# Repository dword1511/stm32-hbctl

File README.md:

# STM32-based half-bridge controller

This firmware code uses an `STM32F042` MCU to generate waveform for a STMicro `L6498` half-bridge driver,
which drives the MOSFETs in the inverter.

This particular inverter delivers 1 MHz AC current for our capacitive power transfer (CPT) project.
It has onboard buttons allowing us to cycle through 1 MHz +/- 100 kHz, with a few kHz of resolution.
It also has USB for ISP/DFU.

Unusual things this firmware does:

* Using HSI48 trimming in conjunction with timer prescaler to deliver a resolution of a few kHz across a large frequency range.
* Using a generic timer (rather than the advanced one) to generate complementary waveforms with dead time.

## General Build Instructions

You will need the following packages (Debian/Ubuntu):

* build-essential
* gcc-arm-none-eabi
* git
* dfu-util

The firmware can be loaded via USB DFU. However, you can also flash and debug via SWD. To do so, install the following package:

* stlink-tools
* gdb-multiarch

This project uses `libopencm3`. It will be automatically checked out during the building process.
To build the firmware, run `make`. To flash it, hold the `ISP/USR` button on the board, connect the board to USB, and then run `make flash-dfu`.

## Special Directions for CPT

Please be aware of the high voltage, especially at matching network's output.

Connect the inverter to the matching network first. Do not power on the inverter without any load.
Connect 12 V DC power to the 12 V port with a 4 mm banana test lead. Connect a variable DC power source to the HV port. Connect the ground together to GND.

Power the board on and observe the LEDs starting to flash. Use the `ISP/USR` button to enable the half-bridge. Then use the same button to cycle through frequencies.
The matching network reaches resonance when the output voltage peaks. Bridge current can be monitored by attaching an oscilloscope probe to the `CSP` pin.

## Publication

This project was part of the following work. Please kindly consider citing the paper as shown:

```
@inproceedings{Capttery,
 author = {Zhang, Chi and Kumar, Sidharth and Bharadia, Dinesh},
 title = {{Capttery: Scalable Battery-like Room-level Wireless Power}},
 booktitle = {Proc. of ACM MobiSys},
 year = {2019},
}
```

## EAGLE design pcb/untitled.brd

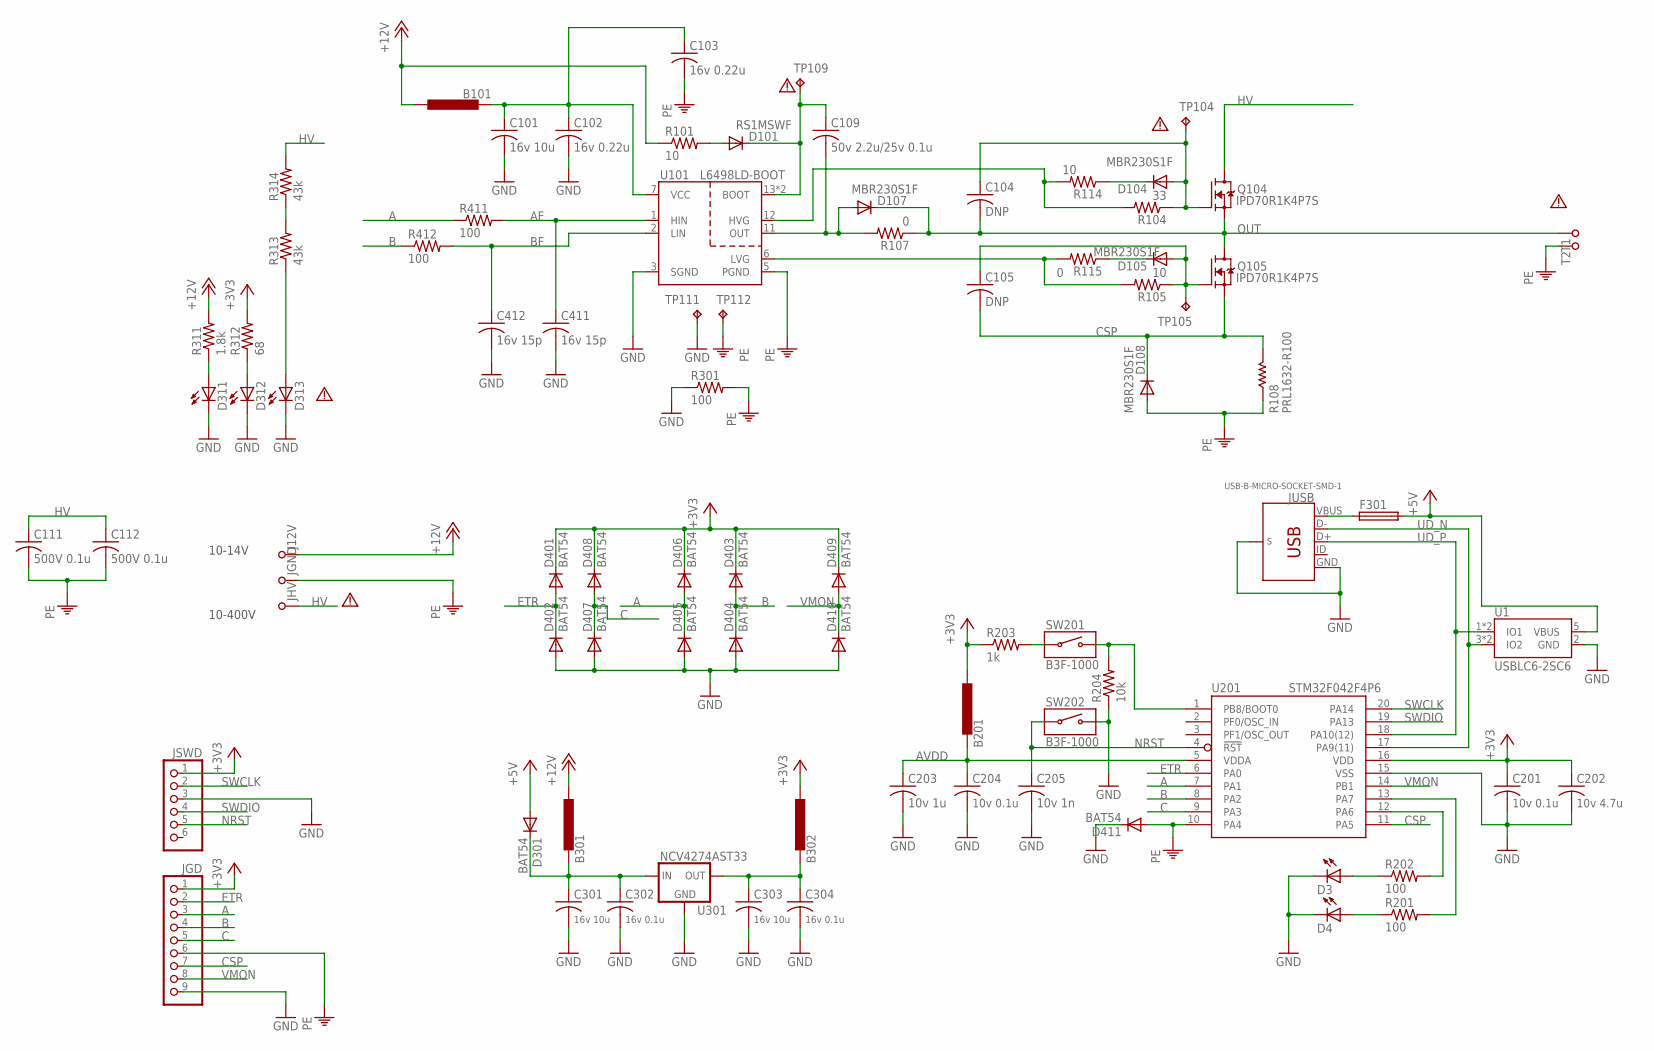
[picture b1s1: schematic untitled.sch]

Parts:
B101, B201, B301, B302: BEAD-0603; 0603
C101, C301, C303: 16v 10u; C0805
C102, C103: 16v 0.22u; C0603
C104, C105: DNP; C0603
C109: 50v 2.2u/25v 0.1u; C0805
C111, C112: 500V 0.1u; C1210
C201, C204: 10v 0.1u; C0603
C202: 10v 4.7u; C0603
C203: 10v 1u; C0603
C205: 10v 1n; C0603
C302, C304: 16v 0.1u; C0603
C411, C412: 16v 15p; C0603
D3, D4, D311, D312, D313: LEDSML0603; SML0603
D101: RS1MSWF; SOD123
D104, D105, D107, D108: MBR230S1F; SOD123
D301, D401, D402, D403, D404, D405, D406, D407, D408, D409, D410, D411: BAT54; SOD323-R
F301: FUSE-0603; 0603
J12V: BANANA_JACKKEYSTONE-575; KEYSTONE-575
JGD: PINHD-1X9/90; 1X09/90
JGND: BANANA_JACKKEYSTONE-575; KEYSTONE-575
JHV: BANANA_JACKKEYSTONE-575; KEYSTONE-575
JSWD: PINHD-1X6/90; 1X06/90
JUSB: USB-B-MICRO-SOCKET-SMD-1
Q104, Q105: IPD70R1K4P7S; TO-252AA
R101, R105, R114: 10; R0603
R104: 33; R0603
R107, R115: 0; R0603
R108: PRL1632-R100; 1206W
R201, R202, R301, R411, R412: 100; R0603
R203: 1k; R0603
R204: 10k; R0603
R311: 1.8k; R0603
R312: 68; R0603
R313, R314: 43k; R0603
SILK1, SILK2, SILK7, SILK11, SILK14: CAUTION-1.3MM
SW201, SW202: B3F-1000; B3F-10XX
T1, T2: TP; PAD-7.5X2.5
TP104, TP105, TP109, TP111, TP112: TPPAD1-13; P1-13
U1: USBLC6-2SC6; SOT-23-6
U101: L6498LD-BOOT; SOIC-14
U201: STM32F042F4P6; TSSOP-20
U301: NCV4274AST33; SOT-223

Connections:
+3V3: B201.2, B302.2, C201.1, C202.1, D401.C, D403.C, D406.C, D408.C, D409.C, JGD.1, JSWD.1, R203.1, R312.2, U201.16 (VDD)
+5V: D301.A, F301.2, U1.5 (VBUS)
+12V: B101.2, B301.2, J12V.P$1, R101.1, R311.2
A: D405.C, D406.A, JGD.3, R411.1, U201.7 (PA1)
AF: C411.1, R411.2, U101.1 (HIN)
AVDD: B201.1, C203.1, C204.1, U201.5 (VDDA)
B: D403.A, D404.C, JGD.4, R412.1, U201.8 (PA2)
BF: C412.1, R412.2, U101.2 (LIN)
C: D407.C, D408.A, JGD.5, U201.9 (PA3)
CSP: C105.2, D108.C, JGD.7, Q105.3 (S), R108.2, U201.11 (PA5)
ETR: D401.A, D402.C, JGD.2, U201.6 (PA0)
GND: C101.2, C102.2, C201.2, C202.2, C203.2, C204.2, C205.2, C301.2, C302.2, C303.2, C304.2, C411.2, C412.2, D3.C, D4.C, D311.C, D312.C, D313.C, D402.A, D404.A, D405.A, D407.A, D410.A, D411.C, JGD.9, JSWD.3, JUSB.GND, JUSB.MT1 (SHIELD), JUSB.MT2 (SHIELD), JUSB.P$1 (SHIELD), JUSB.P$2 (SHIELD), R204.1, R301.1, SW202.3 (B), SW202.4 (B), TP111.TP, U1.2 (GND), U101.3 (SGND), U201.15 (VSS), U301.2 (GND), U301.4 (GND)
HV: C111.1, C112.1, JHV.P$1, Q104.4 (D), R314.2
unnamed: D101.A, R101.2
unnamed: D105.C, R115.1
unnamed: R313.2, R314.1
unnamed: R105.2, R115.2, U101.6 (LVG)
unnamed: C105.1, D105.A, Q105.1 (G), R105.1, TP105.TP
unnamed: D104.C, R114.1
unnamed: R203.2, SW201.1 (COM), SW201.2 (COM)
unnamed: D3.A, R202.1
unnamed: C109.1, D101.C, TP109.TP, U101.13 (BOOT), U101.14 (BOOT)
unnamed: D4.A, R201.1
unnamed: R204.2, SW201.3 (B), SW201.4 (B), U201.1 (PB8/BOOT0)
unnamed: B301.1, C301.1, C302.1, D301.C, U301.1 (IN)
unnamed: F301.1, JUSB.VBUS
unnamed: R202.2, U201.12 (PA6)
unnamed: B302.1, C303.1, C304.1, U301.3 (OUT)
unnamed: B101.1, C101.1, C102.1, C103.1, U101.7 (VCC)
unnamed: R201.2, U201.13 (PA7)
unnamed: D313.A, R313.1
unnamed: C104.1, D104.A, Q104.1 (G), R104.1, TP104.TP
unnamed: R104.2, R114.2, U101.12 (HVG)
unnamed: C109.2, D107.A, R107.2, U101.11 (OUT)
unnamed: D312.A, R312.1
unnamed: D311.A, R311.1
NRST: C205.1, JSWD.5, SW202.1 (COM), SW202.2 (COM), U201.4 (!RST!)
OUT: C104.2, D107.C, Q104.3 (S), Q105.4 (D), R107.1, T1.1
PE: C103.2, C111.2, C112.2, D108.A, D411.A, JGD.6, JGND.P$1, R108.1, R301.2, T2.1, TP112.TP, U101.5 (PGND), U201.10 (PA4)
SWCLK: JSWD.2, U201.20 (PA14)
SWDIO: JSWD.4, U201.19 (PA13)
UD_N: JUSB.D-, U1.3 (IO2), U1.4 (IO2), U201.17 (PA9(11))
UD_P: JUSB.D+, U1.1 (IO1), U1.6 (IO1), U201.18 (PA10(12))
VMON: D409.A, D410.C, JGD.8, U201.14 (PB1)

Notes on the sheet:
10-14V
10-400V

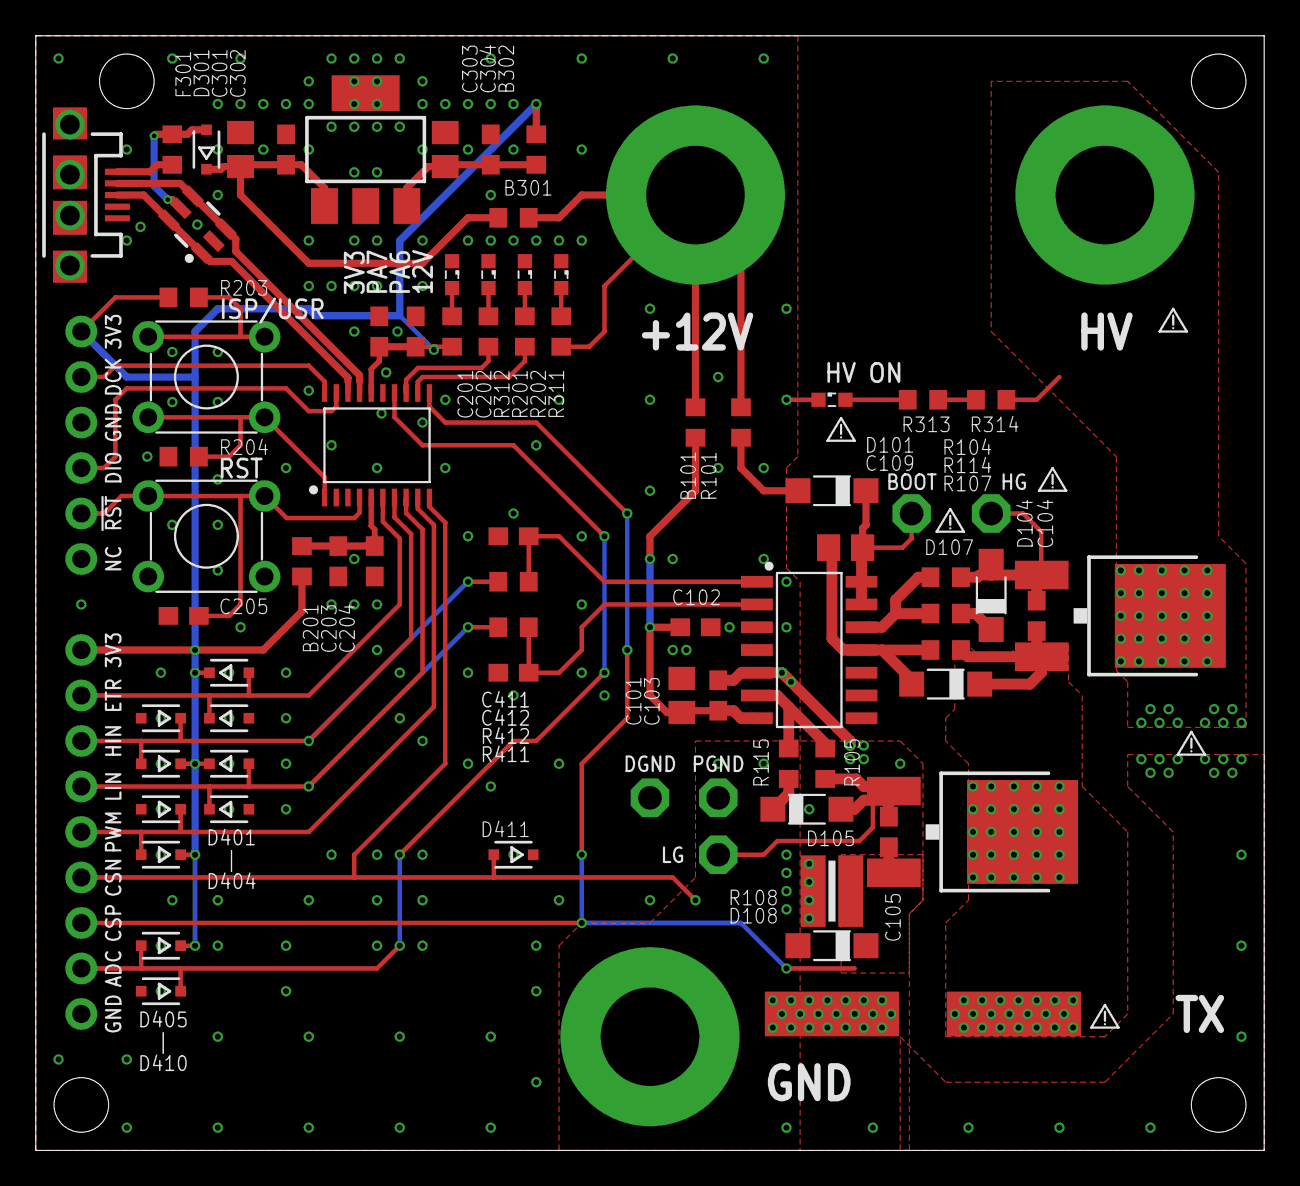
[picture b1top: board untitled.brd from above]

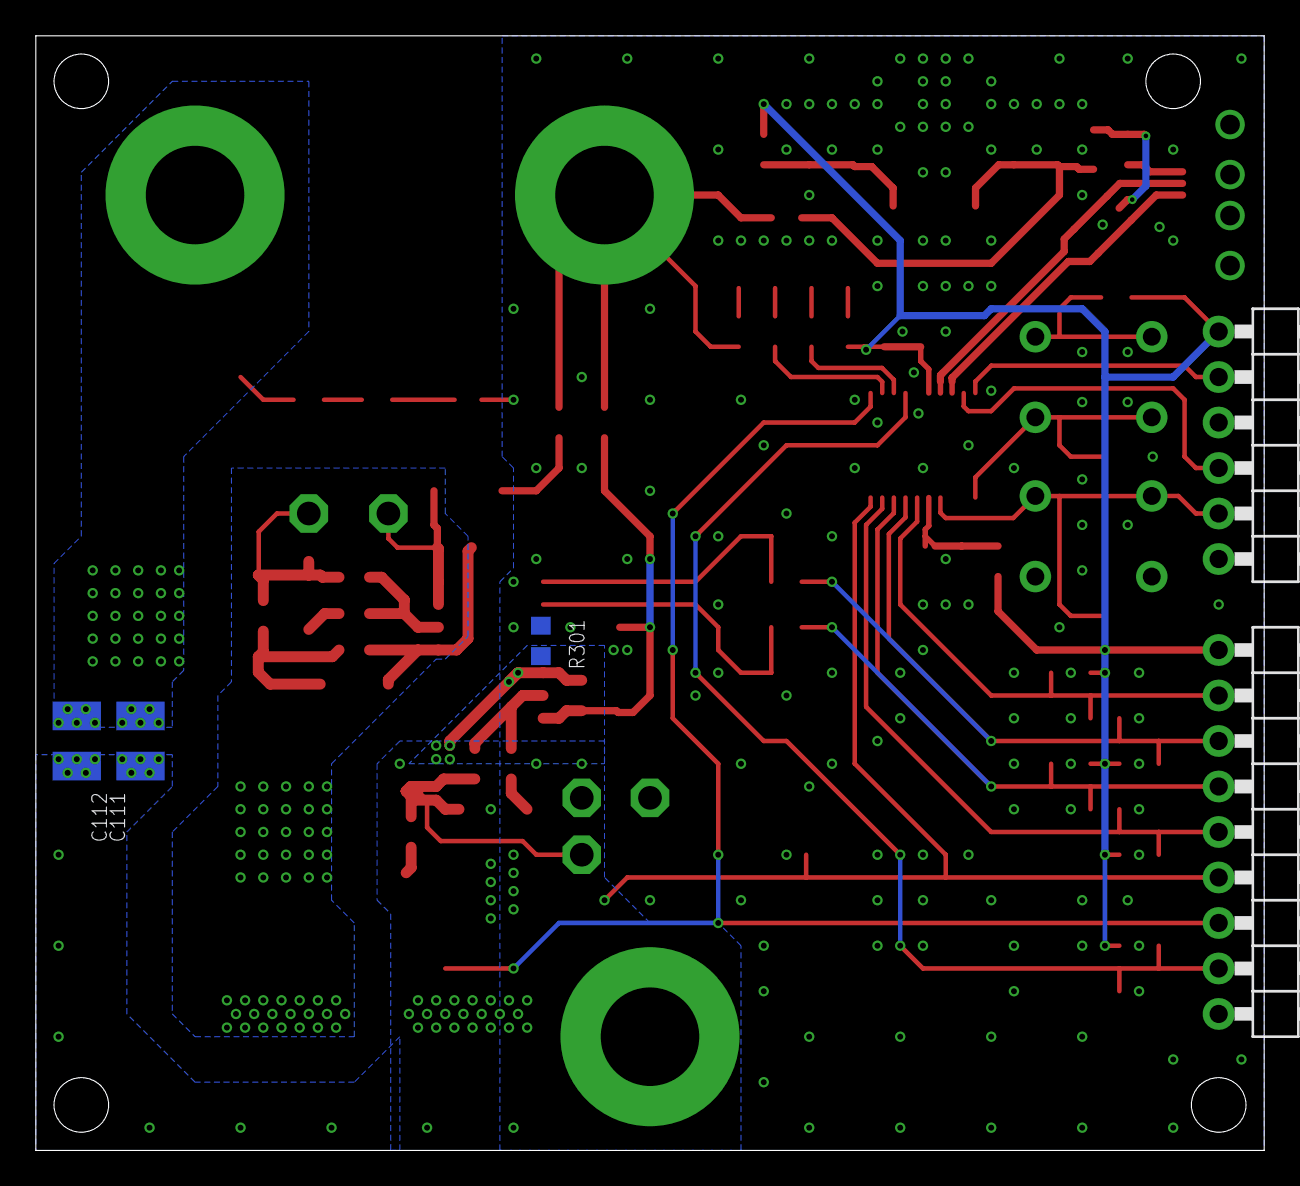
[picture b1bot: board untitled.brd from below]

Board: 2 copper layers, 68.6 x 62.2 mm, 91 parts (5 on the bottom side), 44 nets.

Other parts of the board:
SILK3: CAUTION-1.3MM

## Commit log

2018-06-16 first working version
2018-06-18 lower freqs
2018-06-22 add uart and move tim1 to ch1
2018-07-12 test code for customized hb
2018-08-03 bugfix and improvements
2018-08-05 fine-grained frequency control
2018-08-07 basic stuff
2018-08-07 add debug, fix adc init, add freq limit
2018-08-07 working version
2018-11-12 working port
2018-11-23 fixes and iwdg
2018-11-23 overhaul
2018-11-23 bugfixes
2018-11-24 bugfixes, some bug left
2018-11-24 fix debug
2018-11-25 deadtime adjustments
2018-12-01 latest expe param
2018-12-05 expe setup snapshot
2018-12-12 conference config
2018-12-17 yogaroom
2019-01-04 minor change
2019-01-19 keti demo config
2019-06-09 add pcb and doc
2019-06-09 more instructions
2019-06-09 update doc
